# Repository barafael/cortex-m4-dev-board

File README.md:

# cortex-m4-custom-board
A board with an STM32F401RD LQFP-64 chip and some peripheral headers and mosfet drivers

Schematic:

PCB render:

PCB:

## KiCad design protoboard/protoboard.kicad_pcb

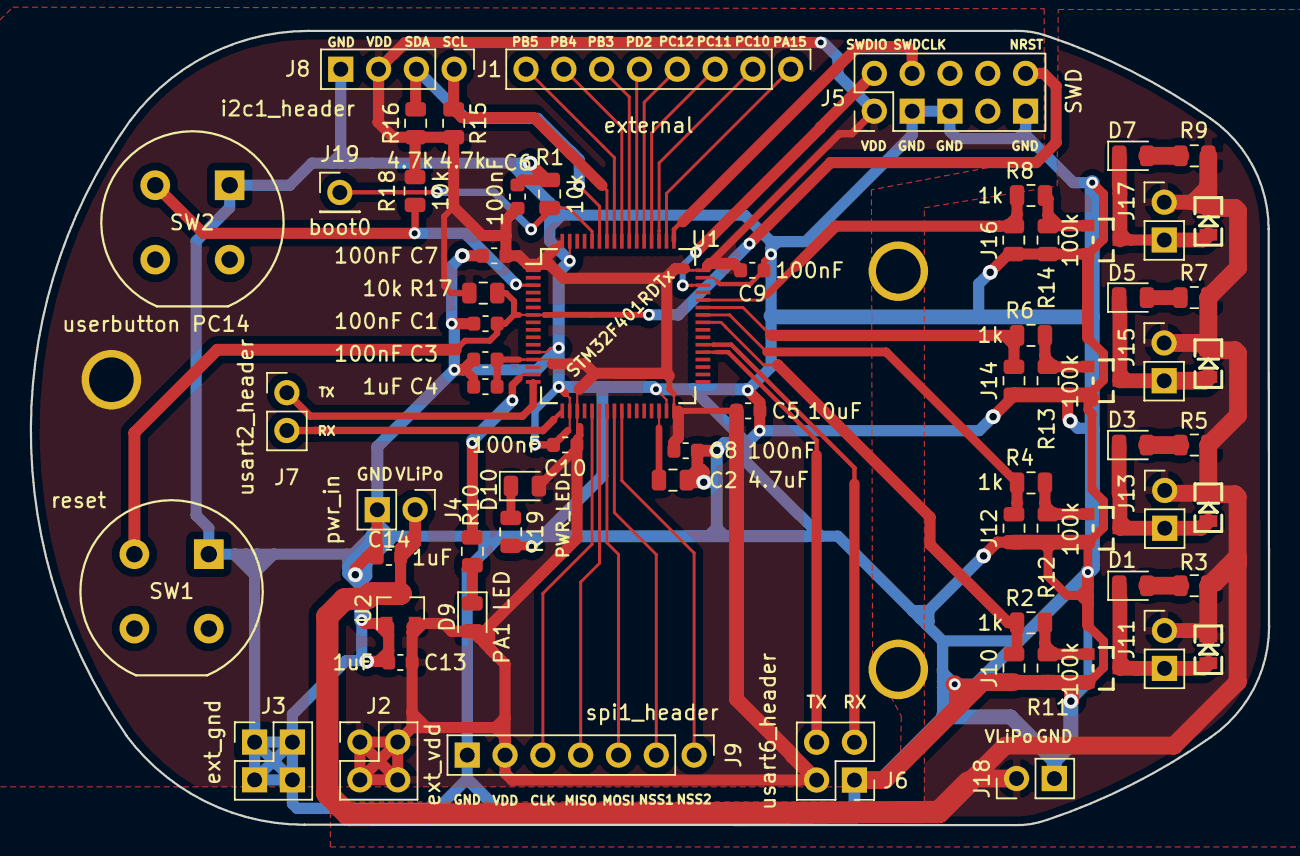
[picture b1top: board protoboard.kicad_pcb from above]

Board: 2 copper layers, 83.2 x 53.4 mm, 71 parts (0 on the bottom side), 47 nets.

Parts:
1pin_prototyping, 1pin_prototyping#2, 1pin_prototyping#3: val**; 1pin_prototyping
C1, C3, C6, C7, C8, C9, C10: 100nF; C_0603_1608Metric
C2: 4.7uF; C_0805_2012Metric
C4, C13, C14: 1uF; C_0603_1608Metric
C5: 10uF; C_0603_1608Metric
D1, D3, D5, D7: LED; LED_0805_2012Metric
D2, D4, D6, D8: DIODE; LED-0805
D9: PA1 LED; LED_0805_2012Metric
D10: PWR_LED; LED_0805_2012Metric
J1: external; PinHeader_1x08_P2.54mm_Vertical
J2: ext_vdd; PinHeader_2x02_P2.54mm_Vertical
J3: ext_gnd; PinHeader_2x02_P2.54mm_Vertical
J4, J18: pwr_in; PinHeader_1x02_P2.54mm_Vertical
J5: SWD; PinHeader_2x05_P2.54mm_Vertical
J6: usart6_header; PinHeader_2x02_P2.54mm_Vertical
J7: usart2_header; PinHeader_1x02_P2.54mm_Vertical
J8: i2c1_header; PinHeader_1x04_P2.54mm_Vertical
J9: spi1_header; PinHeader_1x07_P2.54mm_Vertical
J10, J12, J14, J16: Conn_01x02_Female; R_0805_2012Metric
J11, J13, J15, J17: brushed_out; PinHeader_1x02_P2.54mm_Vertical
J19: boot0; PinHeader_1x01_P2.54mm_Vertical
Q1, Q2, Q3, Q4: MOSFET_N; SOT23_FET
R1, R17, R18: 10k; R_0805_2012Metric
R2, R4, R6, R8: 1k; R_0805_2012Metric
R3, R5, R7, R9, R10, R19: 500; R_0805_2012Metric
R11, R12, R13, R14: 100k; R_0805_2012Metric
R15, R16: 4.7k; R_0805_2012Metric
SW1: reset; Push_E-Switch_KS01Q01
SW2: userbutton PC14; Push_E-Switch_KS01Q01
U1: STM32F401RDTx; LQFP-64_10x10mm_P0.5mm
U2: MCP1700-3302E_TO92; mcp1700

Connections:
GND: C1.2, C2.2, C3.2, C4.2, C5.2, C6.2, C7.2, C8.2, C9.2, C10.2, C13.2, C14.2, J3.1, J3.2, J3.3, J3.4, J4.2, J5.3, J5.5, J5.9, J6.1, J8.4, J9.7, J10.1, J12.1, J14.1, J16.1, J18.2, Q1.S, Q2.S, Q3.S, Q4.S, R1.2, R11.1, R12.1, R13.1, R14.1, R19.2, SW1.2, SW2.2, U1.12, U1.18, U1.31, U1.47, U1.63, U2.1
I2C1_SCL: J8.1, R15.1, U1.58
I2C1_SDA: J8.2, R16.2, U1.59
NRST: C1.1, J5.10, R17.2, SW1.1, U1.7
unnamed: D1.1, D2.A, J11.2, Q1.D
unnamed: D1.2, R3.2
unnamed: D3.1, D4.A, J13.2, Q2.D
unnamed: D3.2, R5.2
unnamed: D5.1, D6.A, J15.2, Q3.D
unnamed: D5.2, R7.2
unnamed: D7.1, D8.A, J17.2, Q4.D
unnamed: D7.2, R9.2
unnamed: D9.1, R10.1
unnamed: D10.1, R19.1
unnamed: Q1.G, R2.1, R11.2
unnamed: Q2.G, R4.1, R12.2
unnamed: Q3.G, R6.1, R13.2
unnamed: Q4.G, R8.1, R14.2
PA15: J1.1, U1.50
PB3: J1.6, U1.55
PB4: J1.7, U1.56
PB5: J1.8, U1.57
PC10: J1.2, U1.51
PC11: J1.3, U1.52
PC12: J1.4, U1.53
PD2: J1.5, U1.54
PWM1: J10.2, R2.2, U1.41
PWM2: J12.2, R4.2, U1.42
PWM3: J14.2, R6.2, U1.43
PWM4: J16.2, R8.2, U1.44
SPI1CLK: J9.5, U1.21
SPI1MISO: J9.4, U1.22
SPI1MOSI: J9.3, U1.23
SPI1NSS1: J9.2, U1.24
SPI1NSS2: J9.1, U1.25
SWDCLK: J5.4, U1.49
SWDIO: J5.2, U1.46
USART2_RX: J7.2, U1.17
USART2_TX: J7.1, U1.16
USART6_RX: J6.3, U1.38
USART6_TX: J6.4, U1.37
VDD: C3.1, C4.1, C5.1, C6.1, C7.1, C8.1, C9.1, C10.1, C13.1, D9.2, D10.2, J2.1, J2.2, J2.3, J2.4, J5.1, J6.2, J8.3, J9.6, R15.2, R16.1, R17.1, R18.1, U1.1, U1.13, U1.19, U1.32, U1.48, U1.64, U2.3
VLiPo: C14.1, D2.K, D4.K, D6.K, D8.K, J4.1, J11.1, J13.1, J15.1, J17.1, J18.1, R3.1, R5.1, R7.1, R9.1, U2.2
boot0: J19.1, R1.1, U1.60
user_button: R18.2, SW2.1, U1.3
user_led: R10.2, U1.15
vcap1: C2.1, U1.30

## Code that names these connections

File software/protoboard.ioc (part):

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Mcu.Name=STM32F401R(D-E)Tx
Mcu.Package=LQFP64
Mcu.UserName=STM32F401RDTx
PA1.GPIOParameters=GPIO_Label
PA1.GPIO_Label=user_led
PA1.Signal=GPIO_Output
PA10.GPIOParameters=GPIO_Label
PA10.GPIO_Label=PWM3
PA10.Signal=S_TIM1_CH3
PA11.GPIOParameters=GPIO_Label
PA11.GPIO_Label=PWM4
PA11.Signal=S_TIM1_CH4
PA13.Mode=Serial_Wire
PA13.Signal=SYS_JTMS-SWDIO
PA14.Mode=Serial_Wire
PA14.Signal=SYS_JTCK-SWCLK
PA2.Mode=Asynchronous
PA2.Signal=USART2_TX
PA3.Mode=Asynchronous
PA3.Signal=USART2_RX
PA5.Mode=Full_Duplex_Master
PA5.Signal=SPI1_SCK
PA6.Mode=Full_Duplex_Master
PA6.Signal=SPI1_MISO
PA7.Mode=Full_Duplex_Master
PA7.Signal=SPI1_MOSI
PA8.GPIOParameters=GPIO_Label
PA8.GPIO_Label=PWM1
PA8.Signal=S_TIM1_CH1
PA9.GPIOParameters=GPIO_Label
PA9.GPIO_Label=PWM2
PA9.Signal=S_TIM1_CH2
PB6.Mode=I2C
PB6.Signal=I2C1_SCL
PB7.Mode=I2C
PB7.Signal=I2C1_SDA
PC14-OSC32_IN.GPIOParameters=GPIO_Label
PC14-OSC32_IN.GPIO_Label=user_button
PC14-OSC32_IN.Signal=GPIO_Output
PC4.GPIOParameters=GPIO_Label
PC4.GPIO_Label=SPI1NSS1
PC4.Signal=GPIO_Output
PC5.GPIOParameters=GPIO_Label
PC5.GPIO_Label=SPI1NSS2
PC5.Signal=GPIO_Output
PC6.Mode=Asynchronous
PC6.Signal=USART6_TX
PC7.Mode=Asynchronous
PC7.Signal=USART6_RX
RCC.HSE_VALUE=25000000
RCC.SYSCLKFreq_VALUE=16000000
board=custom

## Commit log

2018-10-15 Add hardware files
2018-10-15 add image and pdf of schematic
2018-10-19 layout fixes
2018-10-19 add pcb file
2018-10-19 update images
2018-10-21 add protoboard page 1 graphic
2018-10-21 name gpio adresses on pcb
2018-11-10 add netlist
2018-11-10 add sym-lib-table
2018-11-10 add pcb render
2018-11-15 add stm32cubemx project
2020-07-22 Update LICENSE
    The Unlicense is not considered valid in all countries (e.g. Germany). MIT License is, and is not too different.
    As I am the sole copyright holder, I can change this :) it's not like anybody cares, anyway.
